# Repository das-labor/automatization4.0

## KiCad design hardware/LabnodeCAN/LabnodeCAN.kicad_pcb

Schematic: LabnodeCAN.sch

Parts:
C1, C4, C5, C6, C8, C9, C19: 100n; C_0603_1608Metric
C2, C3: 22p; C_0603_1608Metric
C7: 220µ/35V; CP_Elec_6.3x5.7
C10: 470µ/10V; CP_Elec_8x10.5
C11, C13: 1µ; C_0603_1608Metric
C12: 22µ; CP_Elec_4x5.7
C14, C15, C16: 1u; C_0603_1608Metric
C17: 2u; C_0603_1608Metric
C18: 10u; C_0603_1608Metric
D1, D2: 3V6; D_SOT-23_ANK
D3, D6: LED; LED_0603_1608Metric
D4: LL5819; D_MELF
D5: 1N5818; D_DO-41_SOD81_P7.62mm_Horizontal
D7: 1N4148; D_MELF
J1: USB_B_Micro; USB_Micro-B_Amphenol_10118194-0001LF_Horizontal
J2: CAN; IDC-Header_2x05_P2.54mm_Vertical
J3: PWR; BarrelJack_CUI_PJ-102AH_Horizontal
J4: ISP; IDC-Header_2x05_P2.54mm_Vertical
J5: Conn_02x17_Odd_Even; PinHeader_2x17_P2.54mm_Vertical
J6: Conn_02x02_Odd_Even; PinHeader_2x02_P2.54mm_Vertical
JP1: EXTPWR; PinHeader_1x03_P2.54mm_Vertical
JP2: NODEPWR; PinHeader_1x03_P2.54mm_Vertical
L1: 10µ; L_0603_1608Metric
L2: 330µ; L_SMD_95_90
R1, R7, R8, R9, R12: 1k5; R_0603_1608Metric
R2, R3: 68; R_0603_1608Metric
R4: 120; R_0603_1608Metric
R5: 1M; R_1206_3216Metric
R6: 330; R_0603_1608Metric
R10, R11: 33k; R_0603_1608Metric
R13: 390k; R_0603_1608Metric
R14: 4k7; R_0603_1608Metric
U1: ATMEGA32-16AU; TQFP-44_10x10mm_P0.8mm
U2: MCP2515-EST; TSSOP-20_4.4x6.5mm_P0.65mm
U3: LM2574M-5; SOIC-14W_7.5x9.0mm_P1.27mm
U4: MCP2551-I-SN; SOIC-8_3.9x4.9mm_P1.27mm
U5: MIC5504-3.3YM5; SOT-23-5
U6: SSD1306; SSD1306_128x64_backmount
Y1: 16 MHz; Crystal_SMD_HC49-SD

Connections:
+3V3: C13.1, D7.1, J5.33, R14.2, U5.5, U6.6, U6.9, U6.11
+5V: C6.1, C8.1, C9.2, C11.1, C12.1, J4.2, J5.8, JP2.2, L1.1, R1.1, R8.1, R9.1, R10.1, R12.2, U1.5, U1.17, U1.38, U2.19, U2.20, U4.3, U5.1
/CANH: J2.3, U4.7
/CANL: J2.4, U4.6
/CAN_CLK: R4.1, U2.9
/CS_CAN: J5.25, R10.2, U1.44, U2.18
/CS_EXT: J4.3, J5.9, U1.41
/INT_CAN: J5.23, U1.42, U2.13
/MISO: J4.9, J5.29, U1.2, U2.17
/MOSI: J4.1, J5.27, U1.1, U2.16
/PA0: J5.32, U1.37
/PA1: J5.30, U1.36
/PA2: J5.28, U1.35
/PA3: J5.26, U1.34
/PA4: J5.24, U1.33
/PA5: J5.22, U1.32
/PA6: J5.20, U1.31
/PA7: J5.18, U1.30
/PB3: J5.21, U1.43
/PC4: J5.12, U1.23
/PC5: J5.10, U1.24
/PC6: J5.6, U1.25
/PC7: J5.2, U1.26
/PD3: J5.11, U1.12
/PD4: J5.13, U1.13
/PD5: J5.15, U1.14
/PD6: J5.17, U1.15
/PD7: J5.19, U1.16
/RESET: C1.2, J4.5, J5.5, U1.4
/RXD: J4.4, J5.3, U1.9
/SCK: J4.7, J5.31, U1.3, U2.14
/SCL: J5.14, R8.2, U1.19, U6.18
/SDA: J5.16, R9.2, U1.20, U6.19, U6.20
/TXD: J4.6, J5.1, R6.1
/USBM: R1.2, R3.2, U1.22
/USBP: R2.2, U1.11, U1.21
/VUSB: J1.1, JP2.3
GND: C1.1, C2.2, C3.2, C4.2, C5.2, C6.2, C7.2, C8.2, C9.1, C10.2, C11.2, C12.2, C13.2, C14.2, C17.2, C18.2, C19.2, D1.2, D2.2, D3.1, D5.2, D6.1, J1.5, J2.1, J2.2, J2.5, J2.6, J3.2, J3.3, J4.10, J5.4, J5.7, J5.34, J6.3, J6.4, R5.2, R11.2, R13.2, U1.6, U1.18, U1.28, U1.39, U2.4, U2.5, U2.7, U2.10, U3.4 (SGND), U3.5 (ON/~OFF), U3.6 (PGND), U4.2, U5.2, U6.1, U6.8, U6.10, U6.12, U6.13, U6.15, U6.16, U6.17, U6.21, U6.22, U6.23, U6.24, U6.25, U6.29, U6.30
unnamed: C2.1, R4.2, U1.7, Y1.1
unnamed: C3.1, U1.8, Y1.2
unnamed: C4.1, U1.29
unnamed: C5.1, L1.2, U1.27
unnamed: C10.1, JP2.1, L2.2, U3.3 (FB)
unnamed: C14.1, U6.27
unnamed: C15.1, U6.2
unnamed: C15.2, U6.3
unnamed: C16.1, U6.4
unnamed: C16.2, U6.5
unnamed: C17.1, C19.1, U6.28
unnamed: C18.1, D7.2, R14.1, U6.14
unnamed: D1.1, J1.2, R3.1
unnamed: D2.1, J1.3, R2.1
unnamed: D3.2, R7.1
unnamed: D4.2, JP1.2
unnamed: D5.1, L2.1, U3.12 (OUT)
unnamed: D6.2, R12.1
unnamed: J1.6, R5.1
unnamed: J3.1, JP1.1
unnamed: R6.2, U1.10
unnamed: R7.2, U1.40
unnamed: R11.1, U4.8
unnamed: R13.1, U6.26
unnamed: U2.1, U4.1
unnamed: U2.2, U4.4
VBUS: J2.7, J2.8, J2.9, J2.10, JP1.3
VCC: C7.1, D4.1, J6.1, J6.2, U3.10 (VIN)

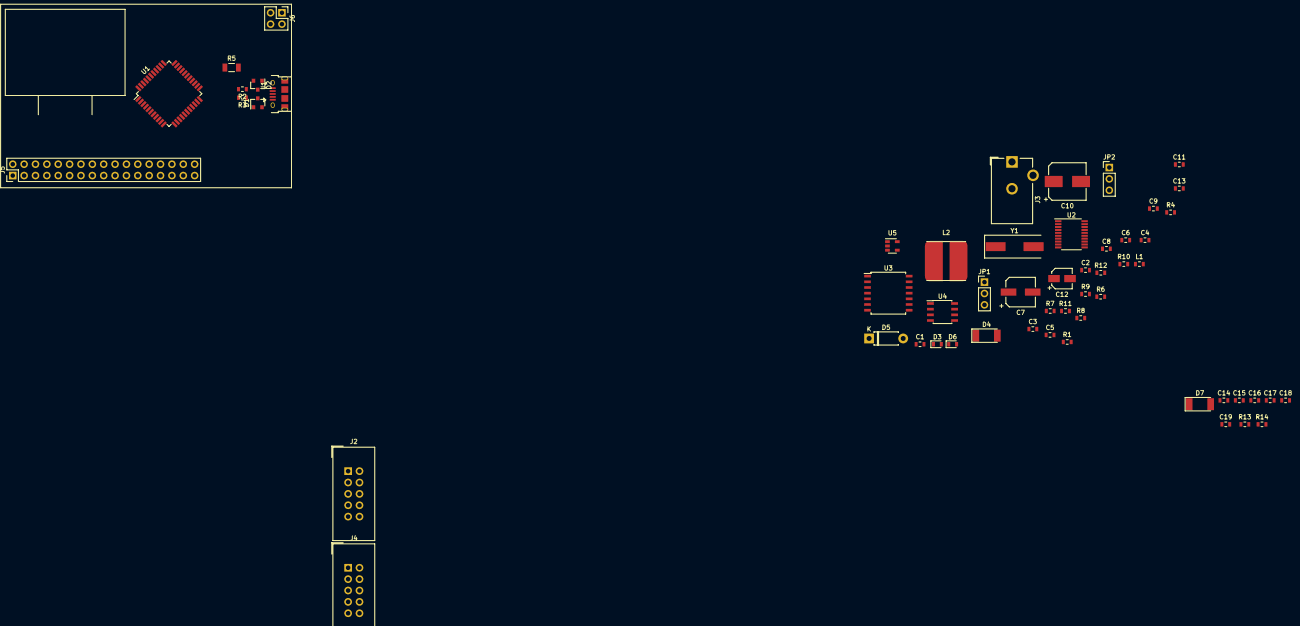
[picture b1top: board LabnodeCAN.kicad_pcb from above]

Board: 2 copper layers, 57 parts (0 on the bottom side), 66 nets, no tracks yet.

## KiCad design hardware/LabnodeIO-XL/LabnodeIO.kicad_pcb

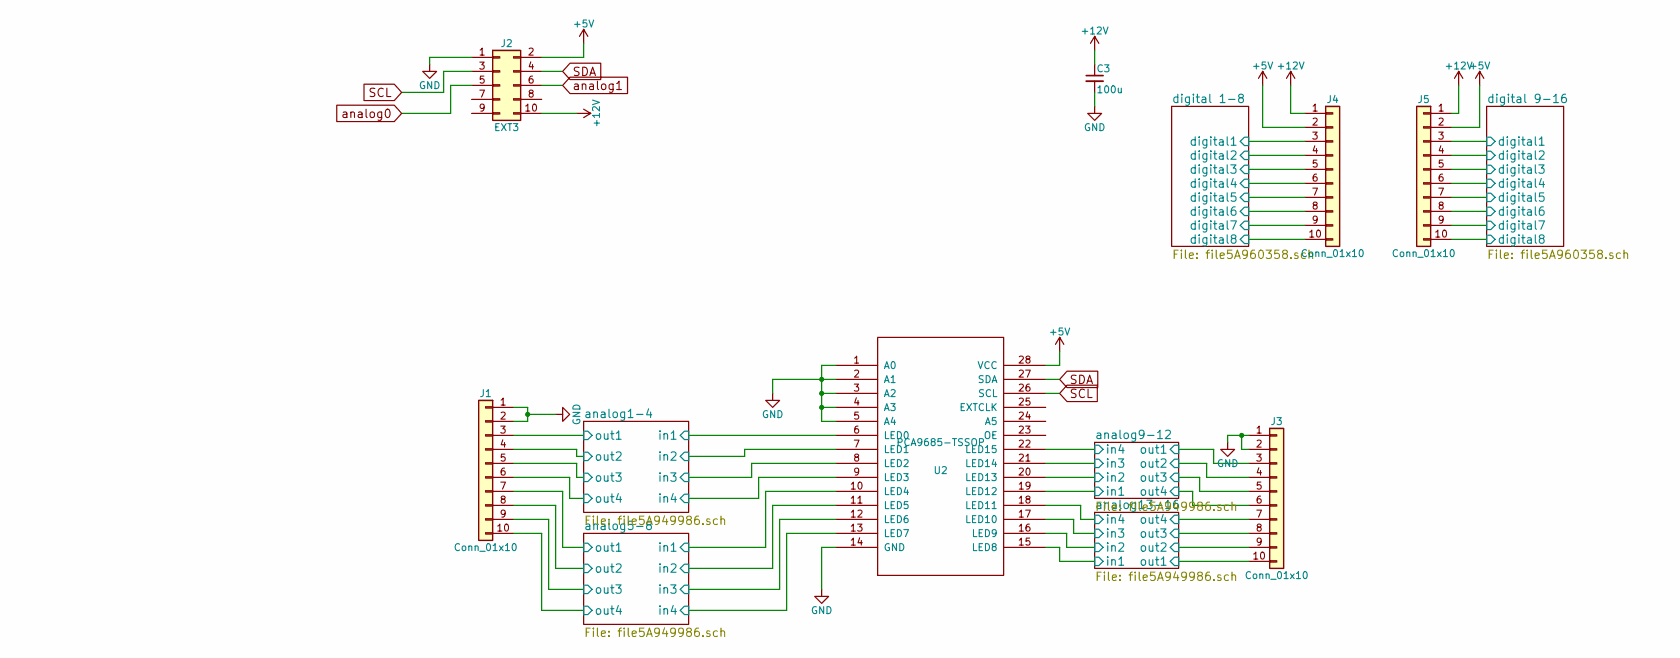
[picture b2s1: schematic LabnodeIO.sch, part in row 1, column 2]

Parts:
C3: 100u; CP_Radial_D8.0mm_P3.80mm
J1, J3, J4, J5: Conn_01x10; MC-0,5-10-G-2,5
J2: EXT3; Pin_Header_Straight_2x05_Pitch2.54mm
U2: PCA9685-TSSOP; TSSOP-28_4.4x9.7mm_Pitch0.65mm

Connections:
+5V: J2.2, J4.2, J5.2, U2.28 (VCC); also elsewhere on the board
+12V: C3.1, J2.10, J4.1, J5.1; also elsewhere on the board
/analog1-4/in1: U2.6 (LED0); also elsewhere on the board
/analog1-4/in2: U2.7 (LED1); also elsewhere on the board
/analog1-4/in3: U2.8 (LED2); also elsewhere on the board
/analog1-4/in4: U2.9 (LED3); also elsewhere on the board
/analog1-4/out1: J1.3; also elsewhere on the board
/analog1-4/out2: J1.4; also elsewhere on the board
/analog1-4/out3: J1.5; also elsewhere on the board
/analog1-4/out4: J1.6; also elsewhere on the board
/analog5-8/in1: U2.10 (LED4); also elsewhere on the board
/analog5-8/in2: U2.11 (LED5); also elsewhere on the board
/analog5-8/in3: U2.12 (LED6); also elsewhere on the board
/analog5-8/in4: U2.13 (LED7); also elsewhere on the board
/analog5-8/out1: J1.7; also elsewhere on the board
/analog5-8/out2: J1.8; also elsewhere on the board
/analog5-8/out3: J1.9; also elsewhere on the board
/analog5-8/out4: J1.10; also elsewhere on the board
/analog9-12/in1: U2.19 (LED12); also elsewhere on the board
/analog9-12/in2: U2.20 (LED13); also elsewhere on the board
/analog9-12/in3: U2.21 (LED14); also elsewhere on the board
/analog9-12/in4: U2.22 (LED15); also elsewhere on the board
/analog9-12/out1: J3.3; also elsewhere on the board
/analog9-12/out2: J3.4; also elsewhere on the board
/analog9-12/out3: J3.5; also elsewhere on the board
/analog9-12/out4: J3.6; also elsewhere on the board
/analog13-16/in1: U2.15 (LED8); also elsewhere on the board
/analog13-16/in2: U2.16 (LED9); also elsewhere on the board
/analog13-16/in3: U2.17 (LED10); also elsewhere on the board
/analog13-16/in4: U2.18 (LED11); also elsewhere on the board
/analog13-16/out1: J3.10; also elsewhere on the board
/analog13-16/out2: J3.9; also elsewhere on the board
/analog13-16/out3: J3.8; also elsewhere on the board
/analog13-16/out4: J3.7; also elsewhere on the board
/digital 1-8/digital1: J4.3; also elsewhere on the board
/digital 1-8/digital2: J4.4; also elsewhere on the board
/digital 1-8/digital3: J4.5; also elsewhere on the board
/digital 1-8/digital4: J4.6; also elsewhere on the board
/digital 1-8/digital5: J4.7; also elsewhere on the board
/digital 1-8/digital6: J4.8; also elsewhere on the board
/digital 1-8/digital7: J4.9; also elsewhere on the board
/digital 1-8/digital8: J4.10; also elsewhere on the board
/digital 9-16/digital1: J5.3; also elsewhere on the board
/digital 9-16/digital2: J5.4; also elsewhere on the board
/digital 9-16/digital3: J5.5; also elsewhere on the board
/digital 9-16/digital4: J5.6; also elsewhere on the board
/digital 9-16/digital5: J5.7; also elsewhere on the board
/digital 9-16/digital6: J5.8; also elsewhere on the board
/digital 9-16/digital7: J5.9; also elsewhere on the board
/digital 9-16/digital8: J5.10; also elsewhere on the board
GND: C3.2, J1.1, J1.2, J2.1, J3.1, J3.2, U2.1 (A0), U2.2 (A1), U2.3 (A2), U2.4 (A3), U2.5 (A4), U2.14 (GND); also elsewhere on the board
SCL: J2.3, U2.26 (SCL); also elsewhere on the board
SDA: J2.4, U2.27 (SDA); also elsewhere on the board

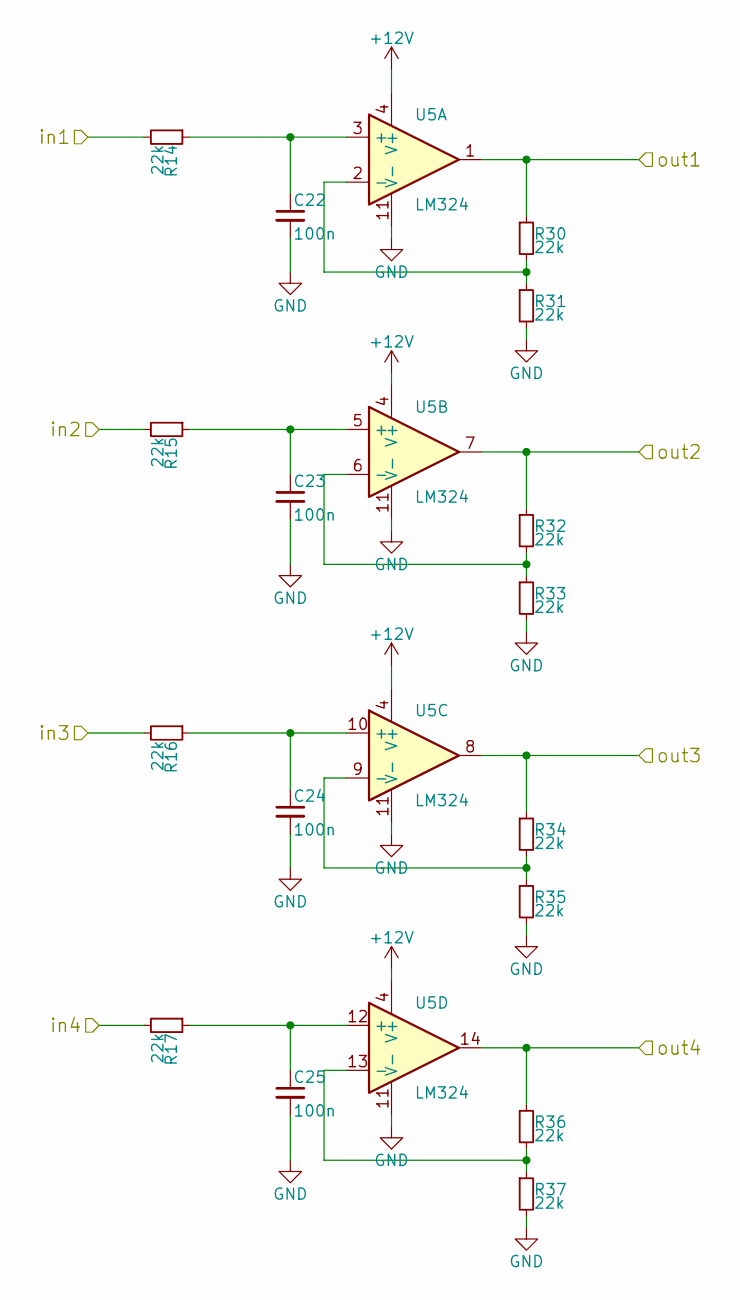
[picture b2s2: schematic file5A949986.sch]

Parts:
C6, C7, C8, C9: 100n; C_0603
R4, R6, R7, R8, R9, R10, R11, R12, R13, R26, R27, R28: 22k; R_0603
U3: LM324; SOIC-14_3.9x8.7mm_Pitch1.27mm

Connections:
+12V: U3.4 (V+); also elsewhere on the board
/analog1-4/in1: R26.2; also elsewhere on the board
/analog1-4/in2: R27.2; also elsewhere on the board
/analog1-4/in3: R28.2; also elsewhere on the board
/analog1-4/out1: R6.1, U3.1; also elsewhere on the board
/analog1-4/out2: R8.1, U3.7; also elsewhere on the board
/analog1-4/out3: R10.1, U3.8; also elsewhere on the board
/analog1-4/out4: R12.1, U3.14; also elsewhere on the board
/analog9-12/in4: R4.2; also elsewhere on the board
GND: C6.2, C7.2, C8.2, C9.2, R7.2, R9.2, R11.2, R13.2, U3.11 (V-); also elsewhere on the board
unnamed: C6.1, R26.1, U3.3 (+)
unnamed: C7.1, R27.1, U3.5 (+)
unnamed: C8.1, R28.1, U3.10 (+)
unnamed: R6.2, R7.1, U3.2 (-)
unnamed: R8.2, R9.1, U3.6 (-)
unnamed: R10.2, R11.1, U3.9 (-)
unnamed: R12.2, R13.1, U3.13 (-)

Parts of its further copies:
C14, C15, C16, C17, C22, C23, C24, C25, C30, C31, C32, C33: 100n; C_0603
R1, R2, R3, R14, R15, R16, R17, R18, R19, R20, R21, R22, R23, R24, R25, R29, R30, R31, R32, R33, R34, R35, R36, R37, R38, R39, R40, R41, R42, R43, R44, R45, R46, R47, R48, R49: 22k; R_0603
U4, U5, U6: LM324; SOIC-14_3.9x8.7mm_Pitch1.27mm

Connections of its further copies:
+12V: U4.4 (V+), U5.4 (V+), U6.4 (V+); also elsewhere on the board
/analog1-4/in4: R29.2; also elsewhere on the board
/analog5-8/in1: R38.2; also elsewhere on the board
/analog5-8/in2: R39.2; also elsewhere on the board
/analog5-8/in3: R40.2; also elsewhere on the board
/analog5-8/in4: R41.2; also elsewhere on the board
/analog5-8/out1: R42.1, U6.1; also elsewhere on the board
/analog5-8/out2: R44.1, U6.7; also elsewhere on the board
/analog5-8/out3: R46.1, U6.8; also elsewhere on the board
/analog5-8/out4: R48.1, U6.14; also elsewhere on the board
/analog9-12/in1: R1.2; also elsewhere on the board
/analog9-12/in2: R2.2; also elsewhere on the board
/analog9-12/in3: R3.2; also elsewhere on the board
/analog9-12/out1: R18.1, U4.1; also elsewhere on the board
/analog9-12/out2: R20.1, U4.7; also elsewhere on the board
/analog9-12/out3: R22.1, U4.8; also elsewhere on the board
/analog9-12/out4: R24.1, U4.14; also elsewhere on the board
/analog13-16/in1: R14.2; also elsewhere on the board
/analog13-16/in2: R15.2; also elsewhere on the board
/analog13-16/in3: R16.2; also elsewhere on the board
/analog13-16/in4: R17.2; also elsewhere on the board
/analog13-16/out1: R30.1, U5.1; also elsewhere on the board
/analog13-16/out2: R32.1, U5.7; also elsewhere on the board
/analog13-16/out3: R34.1, U5.8; also elsewhere on the board
/analog13-16/out4: R36.1, U5.14; also elsewhere on the board
GND: C14.2, C15.2, C16.2, C17.2, C22.2, C23.2, C24.2, C25.2, C30.2, C31.2, C32.2, C33.2, R19.2, R21.2, R23.2, R25.2, R31.2, R33.2, R35.2, R37.2, R43.2, R45.2, R47.2, R49.2, U4.11 (V-), U5.11 (V-), U6.11 (V-); also elsewhere on the board
unnamed: C14.1, R1.1, U4.3 (+)
unnamed: C15.1, R2.1, U4.5 (+)
unnamed: C16.1, R3.1, U4.10 (+)
unnamed: C22.1, R14.1, U5.3 (+)
unnamed: C23.1, R15.1, U5.5 (+)
unnamed: C24.1, R16.1, U5.10 (+)
unnamed: C25.1, R17.1, U5.12 (+)
unnamed: C30.1, R38.1, U6.3 (+)
unnamed: C31.1, R39.1, U6.5 (+)
unnamed: C32.1, R40.1, U6.10 (+)
unnamed: C33.1, R41.1, U6.12 (+)
unnamed: R18.2, R19.1, U4.2 (-)
unnamed: R20.2, R21.1, U4.6 (-)
unnamed: R22.2, R23.1, U4.9 (-)
unnamed: R24.2, R25.1, U4.13 (-)
unnamed: R30.2, R31.1, U5.2 (-)
unnamed: R32.2, R33.1, U5.6 (-)
unnamed: R34.2, R35.1, U5.9 (-)
unnamed: R36.2, R37.1, U5.13 (-)
unnamed: R42.2, R43.1, U6.2 (-)
unnamed: R44.2, R45.1, U6.6 (-)
unnamed: R46.2, R47.1, U6.9 (-)
unnamed: R48.2, R49.1, U6.13 (-)

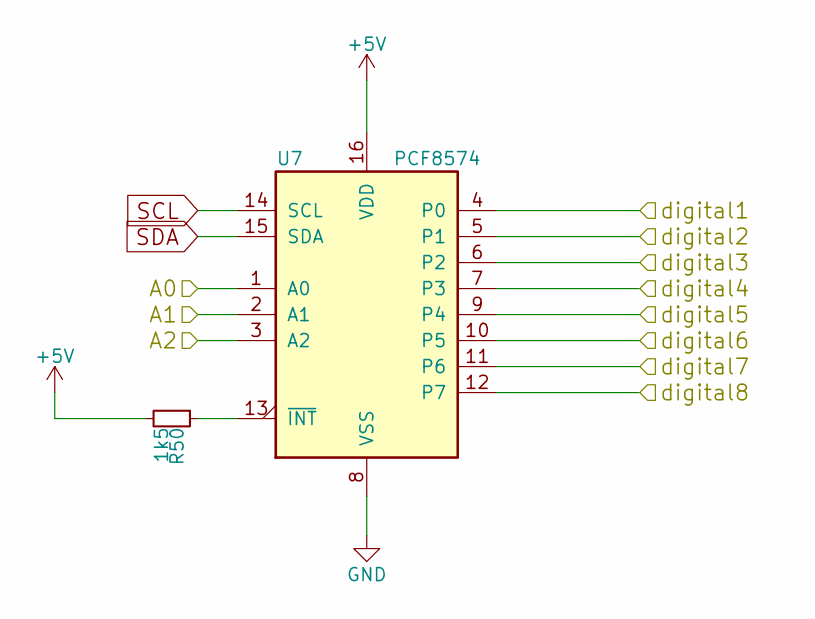
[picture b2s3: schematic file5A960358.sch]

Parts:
R50: 1k5; R_0603
U7: PCF8574; SOIC-16W_7.5x12.8mm_Pitch1.27mm

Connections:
+5V: R50.2, U7.16 (VDD); also elsewhere on the board
/digital 9-16/digital1: U7.4 (P0); also elsewhere on the board
/digital 9-16/digital2: U7.5 (P1); also elsewhere on the board
/digital 9-16/digital3: U7.6 (P2); also elsewhere on the board
/digital 9-16/digital4: U7.7 (P3); also elsewhere on the board
/digital 9-16/digital5: U7.9 (P4); also elsewhere on the board
/digital 9-16/digital6: U7.10 (P5); also elsewhere on the board
/digital 9-16/digital7: U7.11 (P6); also elsewhere on the board
/digital 9-16/digital8: U7.12 (P7); also elsewhere on the board
GND: U7.1 (A0), U7.2 (A1), U7.3 (A2), U7.8 (VSS); also elsewhere on the board
unnamed: R50.1, U7.13 (~INT~)
SCL: U7.14 (SCL); also elsewhere on the board
SDA: U7.15 (SDA); also elsewhere on the board

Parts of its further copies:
R5: 1k5; R_0603
U1: PCF8574; SOIC-16W_7.5x12.8mm_Pitch1.27mm

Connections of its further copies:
+5V: R5.2, U1.1 (A0), U1.16 (VDD); also elsewhere on the board
/digital 1-8/digital1: U1.4 (P0); also elsewhere on the board
/digital 1-8/digital2: U1.5 (P1); also elsewhere on the board
/digital 1-8/digital3: U1.6 (P2); also elsewhere on the board
/digital 1-8/digital4: U1.7 (P3); also elsewhere on the board
/digital 1-8/digital5: U1.9 (P4); also elsewhere on the board
/digital 1-8/digital6: U1.10 (P5); also elsewhere on the board
/digital 1-8/digital7: U1.11 (P6); also elsewhere on the board
/digital 1-8/digital8: U1.12 (P7); also elsewhere on the board
GND: U1.2 (A1), U1.3 (A2), U1.8 (VSS); also elsewhere on the board
unnamed: R5.1, U1.13 (~INT~)
SCL: U1.14 (SCL); also elsewhere on the board
SDA: U1.15 (SDA); also elsewhere on the board

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
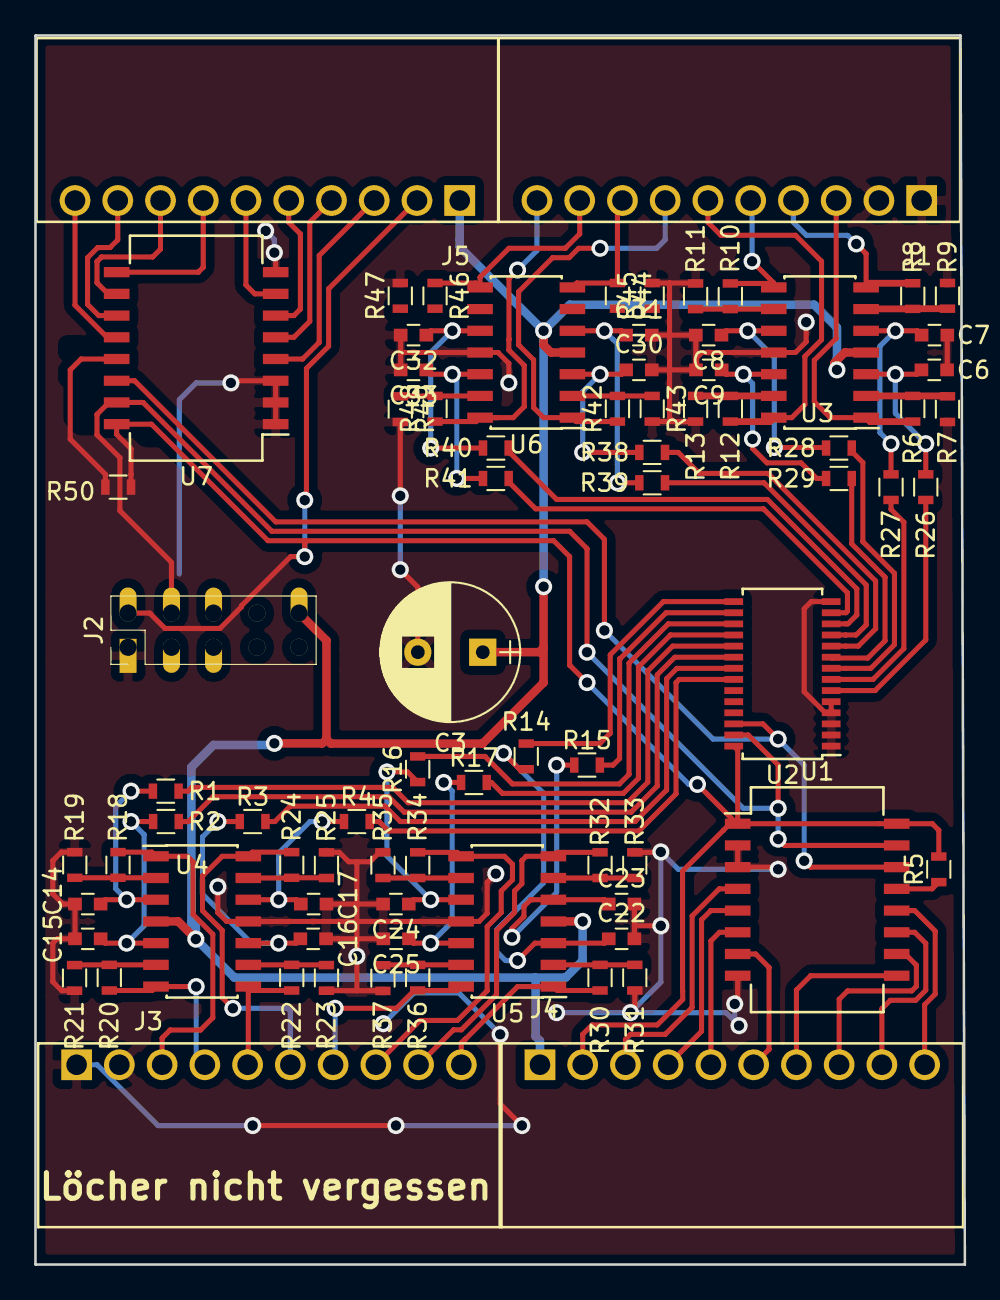
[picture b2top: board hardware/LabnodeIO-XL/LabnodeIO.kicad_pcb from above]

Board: 2 copper layers, 54.4 x 71.9 mm, 79 parts (0 on the bottom side), 87 nets.

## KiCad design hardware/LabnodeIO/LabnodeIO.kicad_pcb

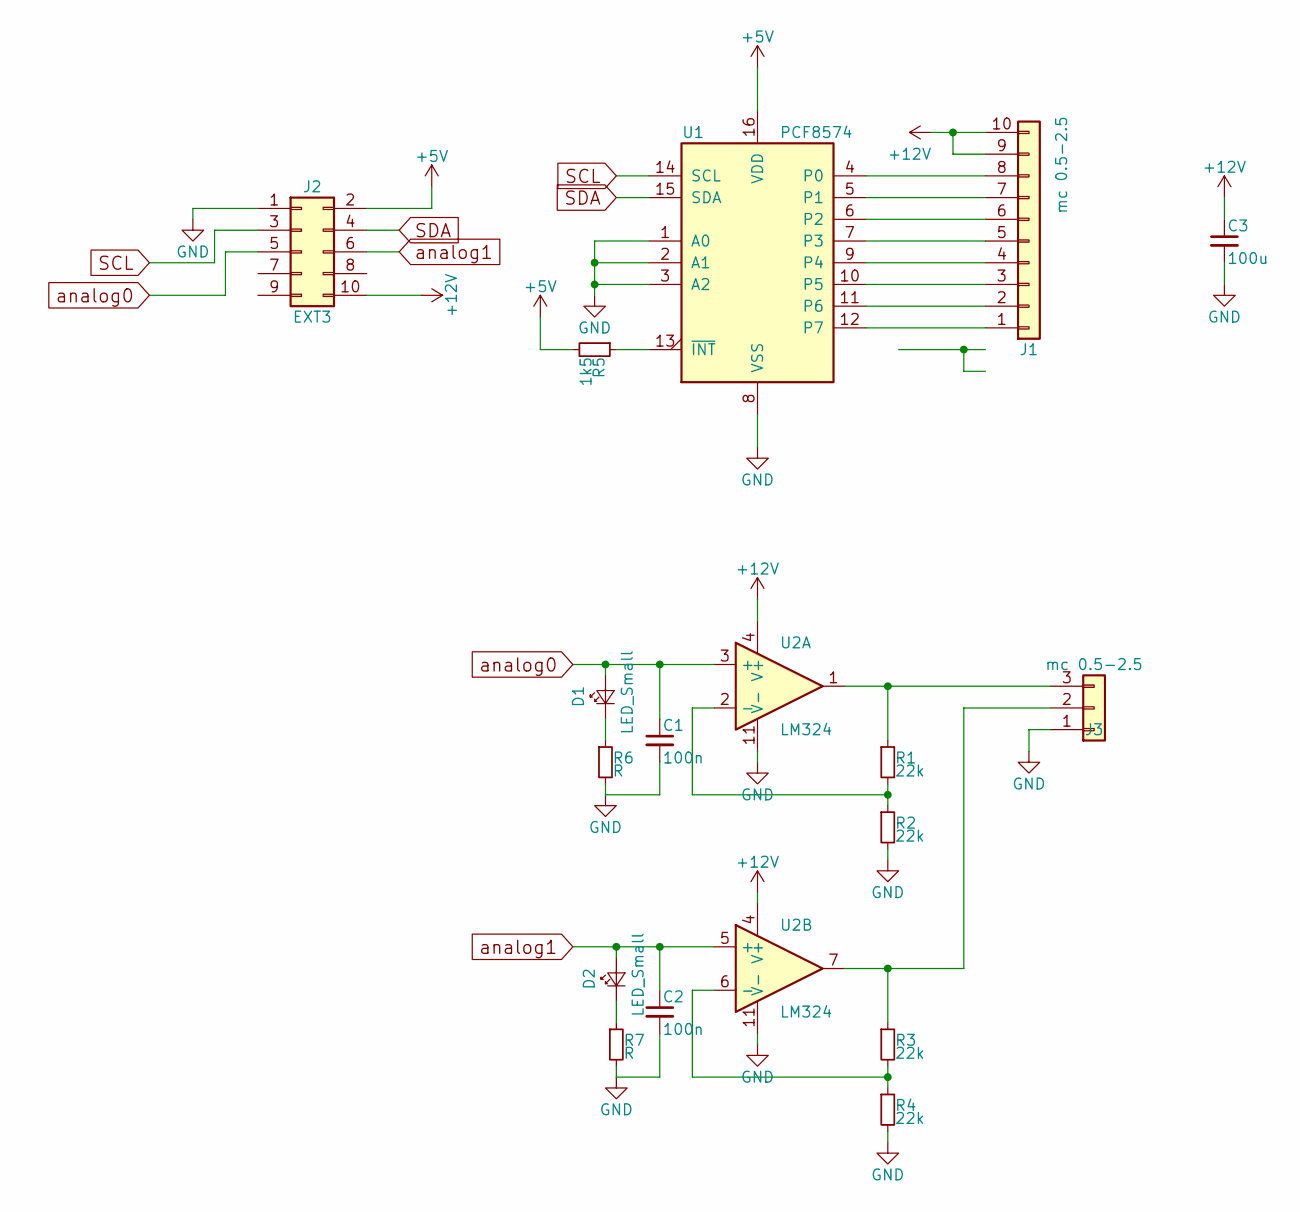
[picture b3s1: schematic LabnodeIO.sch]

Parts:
C1, C2: 100n; C_0805_HandSoldering
C3: 100u; CP_Radial_D8.0mm_P3.80mm
D1, D2: LED_Small; LED_D3.0mm
J1: mc 0.5-2.5; Molex_KK-6410-10_10x2.54mm_Straight
J2: EXT3; Pin_Header_Straight_2x05_Pitch2.54mm
J3: mc 0.5-2.5; Molex_KK-6410-03_03x2.54mm_Straight
R1, R2, R3, R4: 22k; R_0603_HandSoldering
R5: 1k5; R_0603_HandSoldering
R6, R7: R; R_0603_HandSoldering
U1: PCF8574; SOIC-16W_7.5x12.8mm_Pitch1.27mm
U2: LM324; SOIC-14_3.9x8.7mm_Pitch1.27mm

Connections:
+5V: J2.2, R5.2, U1.16 (VDD)
+12V: C3.1, J1.9, J1.10, J2.10, U2.4 (V+)
GND: C1.2, C2.2, C3.2, J2.1, J3.1, R2.2, R4.2, R6.2, R7.2, U1.1 (A0), U1.2 (A1), U1.3 (A2), U1.8 (VSS), U2.11 (V-); also elsewhere on the board
unnamed 3: J3.3, R1.1, U2.1; also elsewhere on the board
unnamed 4: J3.2, R3.1, U2.7; also elsewhere on the board
unnamed: D1.1 (K), R6.1
unnamed: D2.1 (K), R7.1
unnamed: J1.1, U1.12 (P7)
unnamed: J1.2, U1.11 (P6)
unnamed: J1.3, U1.10 (P5)
unnamed: J1.4, U1.9 (P4)
unnamed: J1.5, U1.7 (P3)
unnamed: J1.6, U1.6 (P2)
unnamed: J1.7, U1.5 (P1)
unnamed: J1.8, U1.4 (P0)
unnamed: R1.2, R2.1, U2.2 (-)
unnamed: R3.2, R4.1, U2.6 (-)
unnamed: R5.1, U1.13 (~INT~)
SCL: J2.3, U1.14 (SCL)
SDA: J2.4, U1.15 (SDA)
analog0: C1.1, D1.2 (A), J2.5, U2.3 (+)
analog1: C2.1, D2.2 (A), J2.6, U2.5 (+)

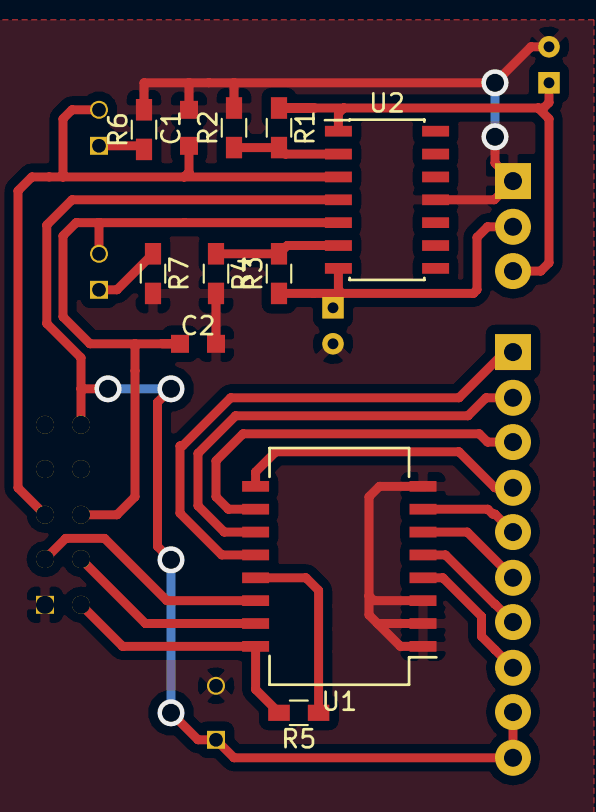
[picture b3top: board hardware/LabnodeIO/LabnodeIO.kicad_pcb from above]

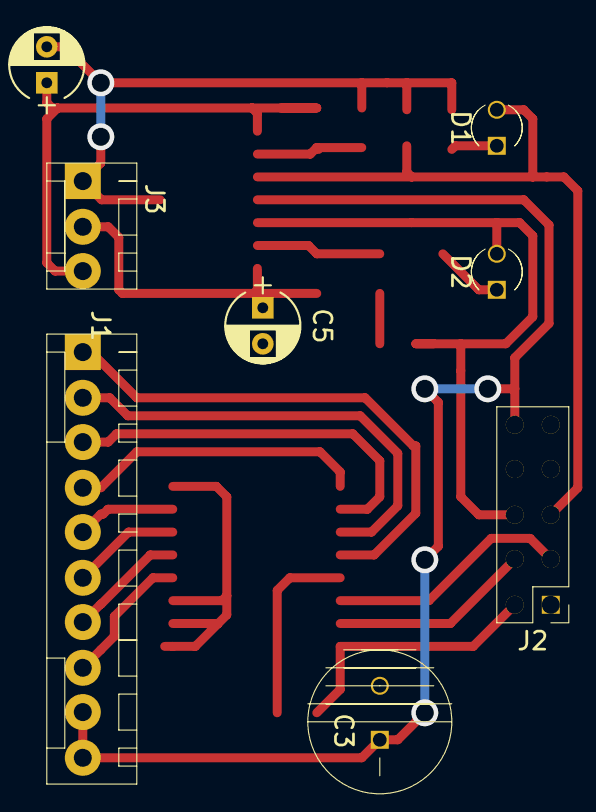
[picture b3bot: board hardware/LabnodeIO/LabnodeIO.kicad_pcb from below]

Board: 2 copper layers, 19 parts (8 on the bottom side), 22 nets.

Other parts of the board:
C4, C5: 100u; CP_Radial_D4.0mm_P2.00mm

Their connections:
GND: C4.2, C5.2; also elsewhere on the board
unnamed 3: C4.1; also elsewhere on the board
unnamed 4: C5.1; also elsewhere on the board

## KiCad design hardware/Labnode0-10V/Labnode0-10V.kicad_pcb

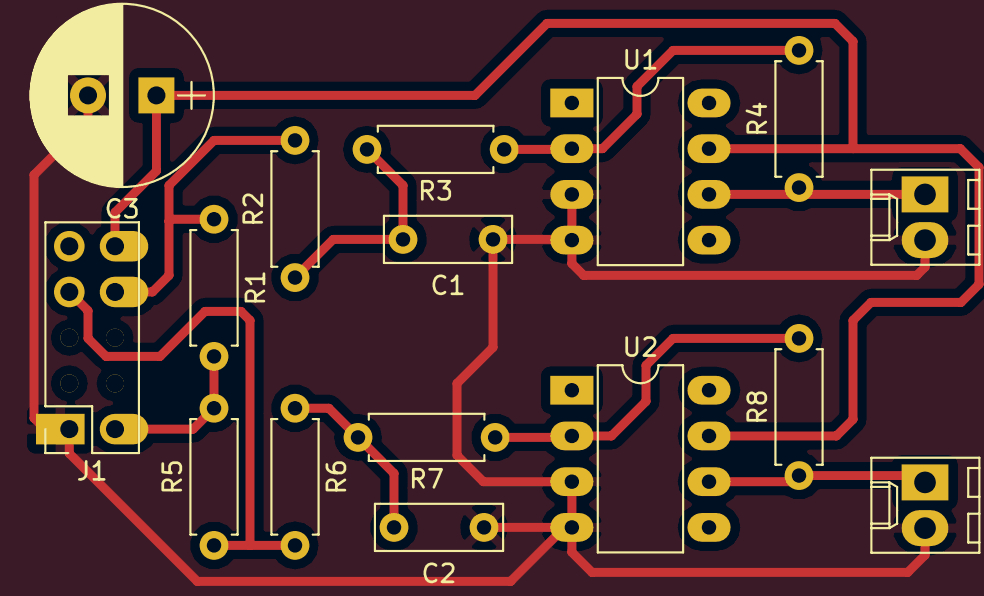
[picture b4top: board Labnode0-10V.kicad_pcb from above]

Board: 2 copper layers, 16 parts (0 on the bottom side), 11 nets.

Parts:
C1, C2: C_Small; C_Rect_L7.0mm_W2.5mm_P5.00mm
C3: C_Small; CP_Radial_D10.0mm_P3.80mm
J1: Conn_02x05_Odd_Even; Socket_Strip_Straight_2x05_Pitch2.54mm
J2, J3: Conn_01x02; Molex_KK-6410-02_02x2.54mm_Straight
R1, R5: 1k5; R_Axial_DIN0207_L6.3mm_D2.5mm_P7.62mm_Horizontal
R2, R6: 22k; R_Axial_DIN0207_L6.3mm_D2.5mm_P7.62mm_Horizontal
R3, R4, R7, R8: R_Small; R_Axial_DIN0207_L6.3mm_D2.5mm_P7.62mm_Horizontal
U1, U2: LM741; DIP-8_W7.62mm_LongPads

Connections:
+5V: J1.2, R1.2, R5.2
+12V: C3.1, J1.10, U1.7, U2.7
/opamp2/in: J1.7, R5.1, R6.2
/opamp2/out: J3.1, R8.1, U2.6
/opamp/in: J1.8, R1.1, R2.2
/opamp/out: J2.1, R4.1, U1.6
GND: C1.1, C2.1, C3.2, J1.1, J2.2, J3.2, U1.3, U1.4, U2.3, U2.4
unnamed: C1.2, R2.1, R3.2
unnamed: C2.2, R6.1, R7.2
unnamed: R3.1, R4.2, U1.2
unnamed: R7.1, R8.2, U2.2

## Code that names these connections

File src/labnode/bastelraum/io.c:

#include <avr/io.h>
#include <util/delay.h>

#include "can_handler.h"
#include "config.h"
#include "io.h"
#include "motion.h"
#include "Bastelcmd.h"
#include "uart_handler.h"


static struct t_pwm_parameter
{
	volatile uint8_t *port;
} pwm_matrix[] =
{
	{ O_PWM00_REG },
	{ O_PWM01_REG },
	{ O_PWM02_REG },
	{ O_PWM03_REG }
};

static uint8_t sreg = 0;

#define HOLD_THRESHOLD 50
#define CLICK_THRESHOLD 2

/*
  -
  arbeitstisch_r_1
  arbeitstisch_r_2
  arbeitstisch_l_1
  arbeitstisch_l_2
  fenster
  mitte
  nische
*/

static void change_shift_reg(uint8_t new_sreg)
{
	for (uint8_t i = 0; i < 8; i++)
	{
		if (new_sreg & (1 << i))
			SREG_PORT |= SREG_DATA;
		else
			SREG_PORT &= ~SREG_DATA;
		SREG_PORT &= ~SREG_CK;
		_delay_us(10);
		SREG_PORT |= SREG_CK;
	}
	SREG_STROBE_PORT &= ~SREG_STROBE;
	_delay_us(10);
	SREG_STROBE_PORT |= SREG_STROBE;
	uart_set_taster_led(sreg);
	can_send_output_status();
}

void set_output_all(uint8_t val)
{
	sreg = val;
	change_shift_reg(sreg);
}

void set_output(uint8_t port, uint8_t val)
{
	if (port < F_REG_COUNT)
	{
		if (val)
			sreg |= 1 << port;
		else
			sreg &= ~(1 << port);
		change_shift_reg(sreg);
	}
}


uint8_t get_outputs()
{
	return sreg;
}


void io_init()
{
	// Init shiftregister
	SREG_STROBE_DDR |= SREG_STROBE;
	SREG_STROBE_PORT |= SREG_STROBE;
	SREG_DDR |= SREG_CK | SREG_DATA;
	SREG_PORT |= SREG_CK;

	change_shift_reg(0); // set default status

	DDRD |= _BV(PD4) | _BV(PD5) | _BV(PD6) | _BV(PD7); // Pins mit pwm als Ausgang

	TCCR2A |= _BV(WGM21) | _BV(WGM20) | _BV(COM2A1) | _BV(COM2B1);	// FastPWM, Set OC2X on Compare Match, clear OC2X at BOTTOM, (non inverting mode).
	TCCR2B |= _BV(CS22);						// clk/64
	TIMSK2 |= _BV(TOIE2);						// Overflow interrupt für timer

	TCCR1A |= _BV(WGM10) | _BV(COM1A1) | _BV(COM1B1);	// FastPWM, Set OC1X on Compare Match, clear OC1X at BOTTOM, (non inverting mode).
	TCCR1B |= _BV(WGM12) | _BV(CS11) | _BV(CS10);		// FastPWM bit 2, clk/64

	// PWM default values

	TCNT2 = 255;   // pwm timer clear
	OCR2A = 255;   // pwm timer compare target
	OCR2B = 255;   // pwm timer compare target

	TCNT1 = 255;   // pwm timer clear
	OCR1A = 255;   // pwm timer compare target
	OCR1B = 255;   // pwm timer compare target

	DDRA  &= ~(_BV(PA4) | _BV(PA7)); // Eingänge Türkontakt / Taster
	PORTA |= _BV(PA4);	// PULLUP Türkontakt
}


void set_pwm(uint8_t port, uint8_t value)
{
	if (port < F_PWM_COUNT)
	{
		(*pwm_matrix[port].port) = value;
		can_send_output_status();
	}
}

void set_pwm_all(uint8_t value)
{
	for (uint8_t i = 0; i < F_PWM_COUNT; i++)
		(*pwm_matrix[i].port) = value;
	can_send_output_status();
}


uint8_t get_pwm(uint8_t port)
{
	return (*pwm_matrix[port].port);
}


void switch_handler()
{
	static uint8_t counter, last_held;
	uint8_t clicked = 0, held = 0;

	if (!(eingang_status & _BV(TASTER_LICHT)))
	{
		counter ++;
		if (counter > HOLD_THRESHOLD)
		{
			held = 1;
			counter = HOLD_THRESHOLD;
		}
	} else
	{
		if (counter > CLICK_THRESHOLD)
			if (counter < HOLD_THRESHOLD)
				clicked = 1;
		counter = 0;
	}

	if (clicked)
	{
		if (sreg)
			set_output_all(0);
		else {
			set_pwm(F_PWM_FENSTER, 200);
			set_pwm(F_PWM_MITTE, 200);
			set_pwm(F_PWM_NISCHE, 200);
			set_output_all(_BV(F_REG_BTISCHR_2) | _BV(F_REG_BTISCHL_1) | _BV(F_REG_FENSTER) | _BV(F_REG_MITTE) | _BV(F_REG_NISCHE));
		}
	}
	if (held)
	{
		// dim
	}
	else if (last_held)
	{
		// change dimmdir
	}
	last_held = held;
}

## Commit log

2018-02-20 empty repo created
2018-02-20 labcontrol submodule added
2018-02-20 TODO added
2018-02-20 can_dimmer added from automization2.0
2018-02-21 0-10V opamp pcb
2018-02-21 TODO updated
2018-02-21 removed submodule
2018-02-21 remove empty file
2018-02-21 replaced labcontrol with working version from svn
2018-02-21 Schaltplan labnodeIO
2018-02-21 layout labnodeIO
2018-02-22 layout fertig
2018-02-22 Ausgangskondensatoren eingefügt
2018-02-23 can_dimmer firmware cleanup, pcf part missing
2018-02-23 PCF8574 support added to can_dimmer
2018-02-23 gitignores added
2018-02-25 PowerCommander state from svn added (untested)
2018-02-26 current status of lounge labnode
2018-02-26 changed powercommander interface of the lounge lights
2018-02-26 5v auf stecker
2018-02-26 Labnode io xl initial commit
2018-02-27 PowerCommander fix (more than 8 output channels possible)
2018-02-28 Platinenlayout und 3d modell angefangen
2018-02-28 pwm chip geroutet
2018-03-01 bastelraum added from svn
2018-03-01 uart also added from svn
2018-03-03 eingangswiderstände hinzugefuegt und geroutet
2018-03-04 bastelraum
2018-03-06 changed TODO
2018-03-14 added new LabnodeCAN schematic
2018-03-15 LabnodeCAN cvpcb finished
2019-09-16 e7p's status...
